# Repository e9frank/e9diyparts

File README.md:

# e9diyparts
A place to put E9 parts that can be made by anyone.  With the appropriate tools.

A place for sharing my parts.

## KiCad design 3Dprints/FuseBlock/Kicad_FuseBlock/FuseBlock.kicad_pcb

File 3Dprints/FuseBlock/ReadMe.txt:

These files are provided without any guarantees.  Use at your own risk!  

When making the circuit board use 2oz copper not 1oz!  

This version of the fuse block and circuit board are for an early E9.  I believe this is considered to be an E3 fuse block.

There are 6 parts to making this fuse block.

1. Blade connectors. Need about 50
2. Fuse connectors.  Need about 20
3. M2x4 screw.       Need 8
4. M2 threaded inserts. Need 8
5. Circuit board.  Just 1 but more is better.
6. ABS 3D printed fuse block.  Just 1 but filament matters.  
Optionally, a printed color card to match the original.

If you look at the parts folder you will see I ordered much more than needed.  If the circuit board is done through a group buy you can easily get the board for less than $3 each.  The Digikey parts can be had for about $30 which includes shipping.  

Having a heated insert tool may help.  However, I have also pushed them in with just the soldering iron tip.  

I printed the fuse block many times trying to get the correct shape.  I also experimented with different filaments.  I thought ABS with carbon fiber would be good because it leaves a nice texture.  But no, it was very brittle and warped allot.  Plain ABS had the best results. The eSun ABS+ worked best for no warping.  Polymaker ABS printed best but warped.  If your not concerned about heat in the car PETG prints very well but it leaves a very glossy surface.  The picture with the back color panel is the final version using eSun ABS with little warping.  

I do not have a fuse cover so it is doubtful that it will fit.  The next time I buy parts from Wallothnesch I plan on getting the cover and updating the fuse block.  

From what I have found on the web about current capacities it appears that the circuit board should be capable of handling the 25A load.  However, I am not an expert on this and could be misreading the information.  Do your own research.  As stated above, use at your own risk.

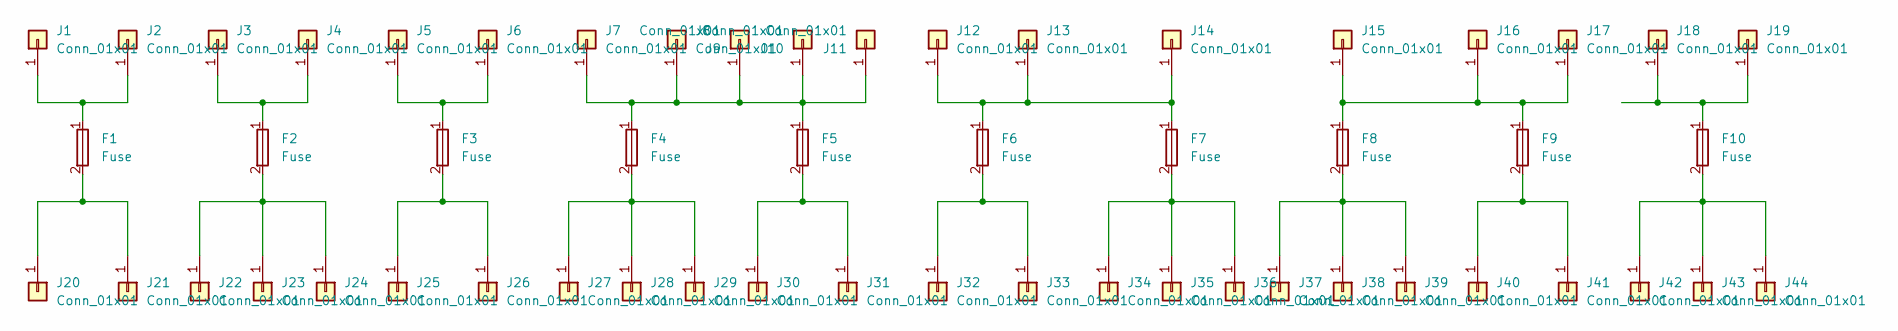
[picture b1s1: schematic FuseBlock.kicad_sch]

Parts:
F1, F2, F3, F4, F5, F6, F7, F8, F9, F10: Fuse; Connector_Fuse_Keystone_3557
J1, J2, J3, J4, J5, J6, J7, J8, J9, J10, J11, J12, J13, J14, J15, J16, J17, J18, J19, J20, J21, J22, J23, J24, J25, J26, J27, J28, J29, J30, J31, J32, J33, J34, J35, J36, J37, J38, J39, J40, J41, J42, J43, J44: Conn_01x01; Connector_Blade

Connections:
unnamed: F1.1, J1.1, J2.1
unnamed: F2.1, J3.1, J4.1
unnamed: F3.1, J5.1, J6.1
unnamed: F4.1, F5.1, J7.1, J8.1, J9.1, J10.1, J11.1
unnamed: F6.1, F7.1, J12.1, J13.1, J14.1
unnamed: F8.1, F9.1, J15.1, J16.1, J17.1
unnamed: F10.1, J18.1, J19.1
unnamed: F1.2, J20.1, J21.1
unnamed: F2.2, J22.1, J23.1, J24.1
unnamed: F3.2, J25.1, J26.1
unnamed: F4.2, J27.1, J28.1, J29.1
unnamed: F5.2, J30.1, J31.1
unnamed: F6.2, J32.1, J33.1
unnamed: F7.2, J34.1, J35.1, J36.1
unnamed: F8.2, J37.1, J38.1, J39.1
unnamed: F9.2, J40.1, J41.1
unnamed: F10.2, J42.1, J43.1, J44.1

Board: 2 copper layers, 54 parts (0 on the bottom side), 17 nets, no tracks yet.

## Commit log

2024-06-15 First update
2024-06-15 Want to see if the mirror will auto update git.
2024-06-15 Added the weber synchrometer 3d print
2024-06-15 Added not used yet warning.
2024-06-23 Added the fuse block
2024-12-08 backup files
2025-02-04 Updated for the fuse block after the cover was added with a document
2025-02-04 Updated document with links
2025-03-31 Added small documents and their images.
2025-04-12 Added adhesives and converted docs to pdf
2025-04-12 Fuseblock pdf
2025-05-26 Relay base delivery
2025-06-07 Added plug for high beam and horn
2025-06-08 Added dip and relay plugs
2025-08-03 Added the gasket for the tail light TailLightHousing
2025-09-20 Added scans of the key cover on the steering column
